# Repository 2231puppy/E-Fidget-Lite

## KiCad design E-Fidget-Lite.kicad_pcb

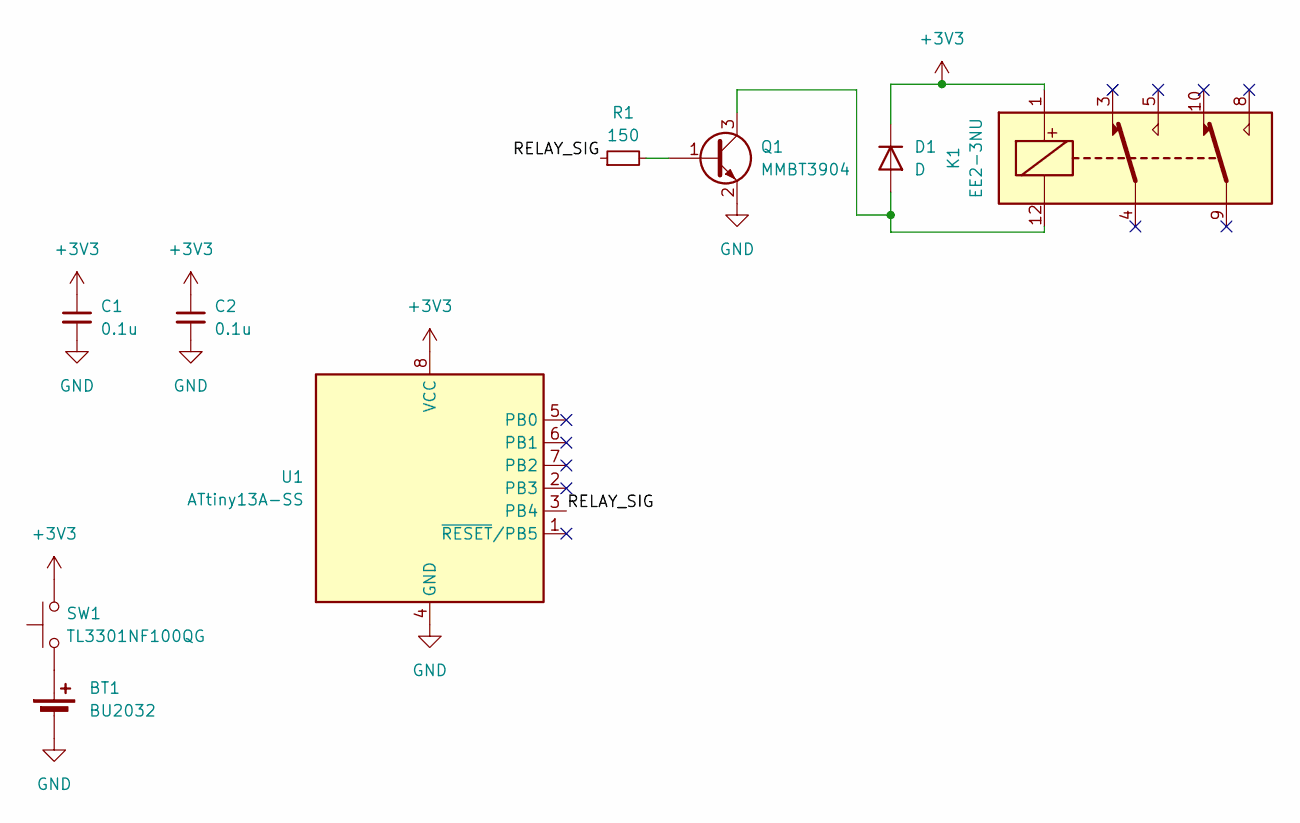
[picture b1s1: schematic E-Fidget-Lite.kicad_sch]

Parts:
BT1: BU2032; BAT_BU2032-1-HD-G
C1, C2: 0.1u; C_0402_1005Metric
D1: D; D_SOD-123
K1: EE2-3NU; Relay_DPDT_Kemet_EC2
Q1: MMBT3904; SOT-23
R1: 150; R_0402_1005Metric
SW1: TL3301NF100QG; SW_Push_1P1T_NO_6x6mm_H9.5mm
U1: ATtiny13A-SS; SOIC-8_3.9x4.9mm_P1.27mm

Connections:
+3V3: C1.1, C2.1, D1.1 (K), K1.1, SW1.2, U1.8 (VCC)
/RELAY_SIG: R1.1, U1.3 (PB4)
GND: BT1.2 (-), C1.2, C2.2, Q1.2 (E), U1.4 (GND)
unnamed: BT1.1 (+), SW1.1
unnamed: D1.2 (A), K1.12, Q1.3 (C)
unnamed: Q1.1 (B), R1.2

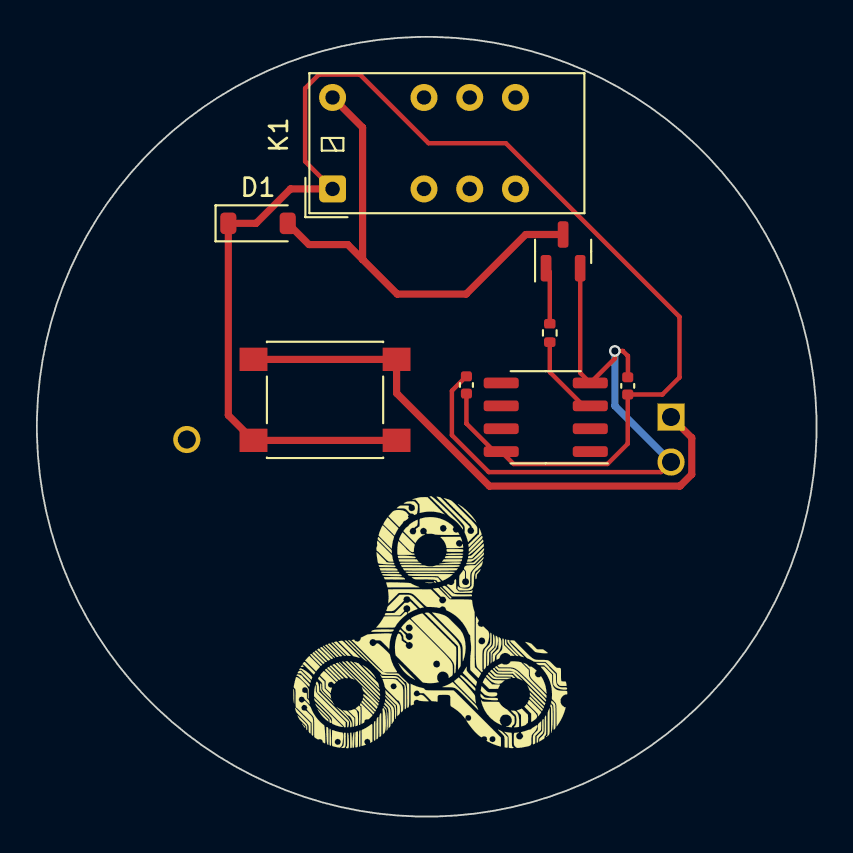
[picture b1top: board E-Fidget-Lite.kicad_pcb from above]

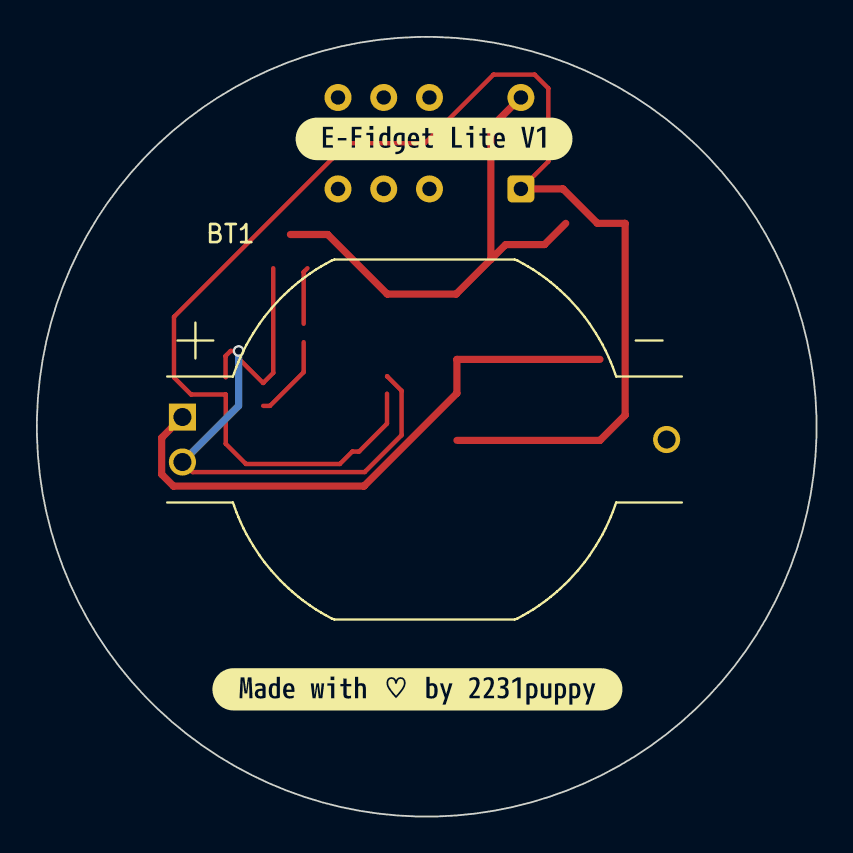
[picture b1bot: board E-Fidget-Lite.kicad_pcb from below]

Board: 2 copper layers, 43.3 x 43.3 mm, 11 parts (3 on the bottom side), 6 nets.

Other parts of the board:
kibuzzard-6472B1FB: G***; kibuzzard-6472B1FB
kibuzzard-6472B22C: G***; kibuzzard-6472B22C

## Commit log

2023-06-19 Here we go again!
